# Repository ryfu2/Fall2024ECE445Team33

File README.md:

# Fall2024ECE445Team33
We are Team33 and this is our git repo for our ECE445 project:

AMADEUS

Augmented Modular AI Dialogue and Exchange User System 

It contains all the files/codes we have created and notes we have taken

There are more details in our design document, feel free to look around!

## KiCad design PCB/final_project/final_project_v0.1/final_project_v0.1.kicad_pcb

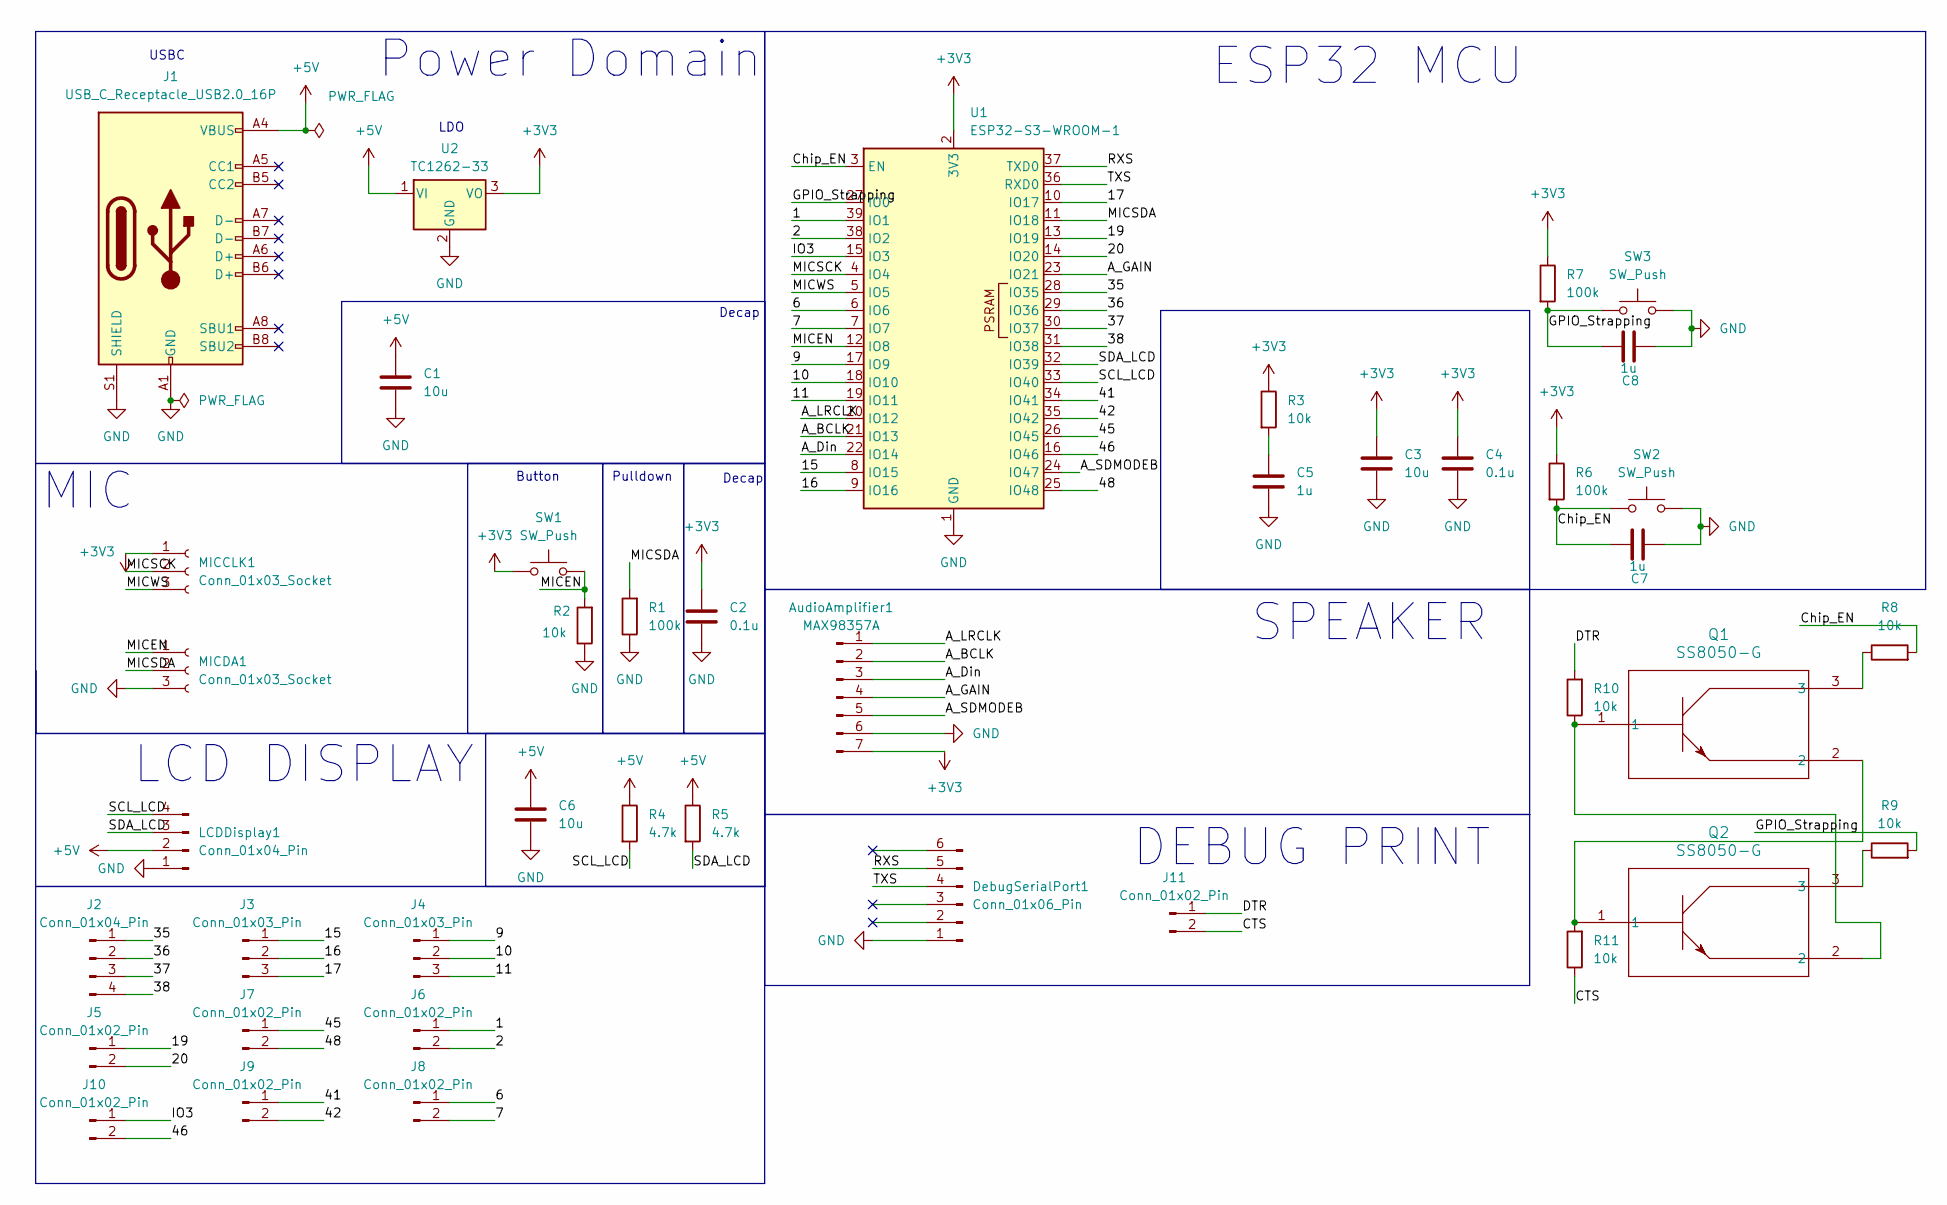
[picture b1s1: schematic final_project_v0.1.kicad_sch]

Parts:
AudioAmplifier1: MAX98357A; PinHeader_1x07_P2.54mm_Vertical
C1, C3, C6: 10u; C_0805_2012Metric_Pad1.18x1.45mm_HandSolder
C2, C4: 0.1u; C_0805_2012Metric_Pad1.18x1.45mm_HandSolder
C5, C7, C8: 1u; C_0805_2012Metric_Pad1.18x1.45mm_HandSolder
DebugSerialPort1: Conn_01x06_Pin; PinHeader_1x06_P2.54mm_Vertical
J1: USB_C_Receptacle_USB2.0_16P; USB_C_Receptacle_GCT_USB4085
J2: Conn_01x04_Pin; PinHeader_1x04_P2.54mm_Vertical
J3, J4: Conn_01x03_Pin; PinHeader_1x03_P2.54mm_Vertical
J5, J6, J7, J8, J9, J10, J11: Conn_01x02_Pin; PinHeader_1x02_P2.54mm_Vertical
LCDDisplay1: Conn_01x04_Pin; PinHeader_1x04_P2.54mm_Vertical
MICCLK1: Conn_01x03_Socket; PinHeader_1x03_P2.54mm_Vertical
MICDA1: Conn_01x03_Socket; PinHeader_1x03_P2.54mm_Vertical
Q1, Q2: SS8050-G; TRAN_SS8050-G_CIP
R1, R6, R7: 100k; R_0805_2012Metric_Pad1.20x1.40mm_HandSolder
R2, R3, R8, R9, R10, R11: 10k; R_0805_2012Metric_Pad1.20x1.40mm_HandSolder
R4, R5: 4.7k; R_0805_2012Metric_Pad1.20x1.40mm_HandSolder
SW1, SW2, SW3: SW_Push; SW_PUSH_6mm_H4.3mm
U1: ESP32-S3-WROOM-1
U2: TC1262-33; SOT-223-3_TabPin2

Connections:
+3V3: AudioAmplifier1.7, C2.1, C3.1, C4.1, MICCLK1.1, R3.1, R6.1, R7.1, SW1.1, U1.2 (3V3), U2.3 (VO)
+5V: C1.1, C6.1, J1.A4 (VBUS), J1.A9 (VBUS), J1.B4 (VBUS), J1.B9 (VBUS), LCDDisplay1.2, R4.1, R5.1, U2.1 (VI)
/1: J6.1, U1.39 (IO1)
/2: J6.2, U1.38 (IO2)
/6: J8.1, U1.6 (IO6)
/7: J8.2, U1.7 (IO7)
/9: J4.1, U1.17 (IO9)
/10: J4.2, U1.18 (IO10)
/11: J4.3, U1.19 (IO11)
/15: J3.1, U1.8 (IO15)
/16: J3.2, U1.9 (IO16)
/17: J3.3, U1.10 (IO17)
/19: J5.1, U1.13 (IO19)
/20: J5.2, U1.14 (IO20)
/35: J2.1, U1.28 (IO35)
/36: J2.2, U1.29 (IO36)
/37: J2.3, U1.30 (IO37)
/38: J2.4, U1.31 (IO38)
/41: J9.1, U1.34 (IO41)
/42: J9.2, U1.35 (IO42)
/45: J7.1, U1.26 (IO45)
/46: J10.2, U1.16 (IO46)
/48: J7.2, U1.25 (IO48)
/A_BCLK: AudioAmplifier1.2, U1.21 (IO13)
/A_Din: AudioAmplifier1.3, U1.22 (IO14)
/A_GAIN: AudioAmplifier1.4, U1.23 (IO21)
/A_LRCLK: AudioAmplifier1.1, U1.20 (IO12)
/A_SDMODEB: AudioAmplifier1.5, U1.24 (IO47)
/CTS: J11.2, R11.1
/Chip_EN: C7.1, R6.2, R8.2, SW2.1, U1.3 (EN)
/DTR: J11.1, R10.2
/GPIO_Strapping: C8.1, R7.2, R9.2, SW3.1, U1.27 (IO0)
/IO3: J10.1, U1.15 (IO3)
/MICEN: MICDA1.1, R2.2, SW1.2, U1.12 (IO8)
/MICSCK: MICCLK1.2, U1.4 (IO4)
/MICSDA: MICDA1.2, R1.2, U1.11 (IO18)
/MICWS: MICCLK1.3, U1.5 (IO5)
/RXS: DebugSerialPort1.5, U1.37 (TXD0)
/SCL_LCD: LCDDisplay1.4, R4.2, U1.33 (IO40)
/SDA_LCD: LCDDisplay1.3, R5.2, U1.32 (IO39)
/TXS: DebugSerialPort1.4, U1.36 (RXD0)
GND: AudioAmplifier1.6, C1.2, C2.2, C3.2, C4.2, C5.2, C6.2, C7.2, C8.2, DebugSerialPort1.1, J1.A1 (GND), J1.A12 (GND), J1.B1 (GND), J1.B12 (GND), J1.S1 (SHIELD), LCDDisplay1.1, MICDA1.3, R1.1, R2.1, SW2.2, SW3.2, U1.1 (GND), U1.40 (GND), U1.41 (GND), U2.2 (GND)
unnamed: C5.1, R3.2
unnamed: Q1.1, Q2.2, R10.1
unnamed: Q1.2, Q2.1, R11.2
unnamed: Q1.3, R8.1
unnamed: Q2.3, R9.1

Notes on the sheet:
LCD DISPLAY
Decap
Power Domain
Button
USBC
ESP32 MCU
MIC
LDO
SPEAKER
DEBUG PRINT
Pulldown

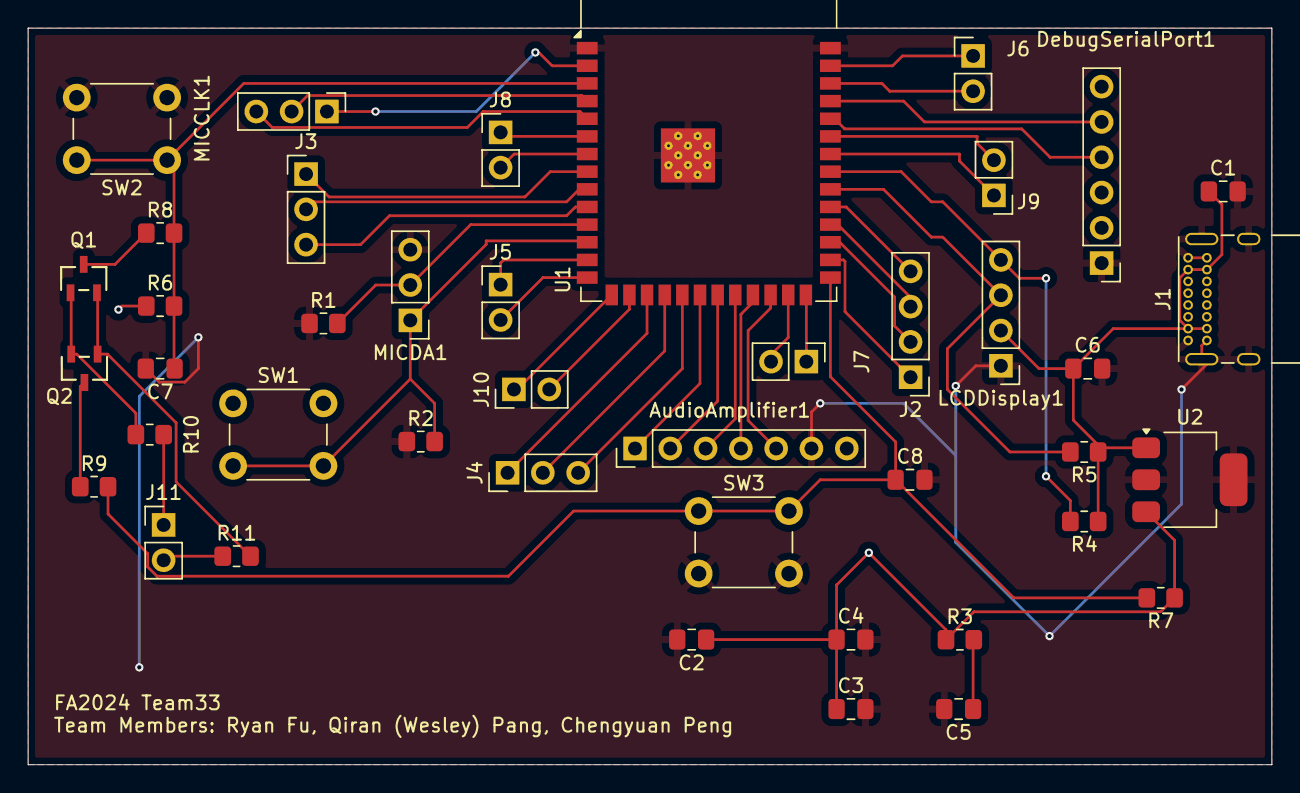
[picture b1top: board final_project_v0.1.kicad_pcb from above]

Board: 2 copper layers, 89.5 x 53.0 mm, 42 parts (0 on the bottom side), 47 nets.

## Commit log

2024-09-24 Repo Created
2024-12-04 Notebook Update
2024-12-04 adding files to notebook
2024-12-04 add documents, wav_receiver python file, and arduino files
2024-12-12 adding README for all code files:
2024-12-12 upload Qiran's README note
2024-12-12 fixing README format
2024-12-12 Moved Qiran's folder to notebooks/
2024-12-13 added notebooks folder
2024-12-13 added Chengyuan's notebook
